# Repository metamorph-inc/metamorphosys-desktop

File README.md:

# metamorphosys-desktop
The **Metamorphosys** tools are used for electronics design and analysis.

_NOTE: This desktop version will soon be replaced by [metamorphosys-web](https://github.com/metamorph-inc/metamorphosys-web). Click over to that repository for a **[live demo](https://github.com/metamorph-inc/metamorphosys-web)**._

# Installer and Documentation
Visit the [alpha release](http://www.metamorphsoftware.com/alpha/) page for:
- Windows Installer
- Example Models
- Walkthrough Tutorials
- Tool Documentation

# Building
To compile the tools from scratch, see [BUILD.md](BUILD.md).

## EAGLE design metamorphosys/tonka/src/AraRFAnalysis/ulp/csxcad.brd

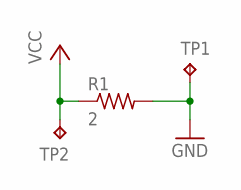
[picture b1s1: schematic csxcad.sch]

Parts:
R1: 2; R0603
TP1, TP2: TPB2,54; B2,54

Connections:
GND: R1.2, TP1.TP
VCC: R1.1, TP2.TP

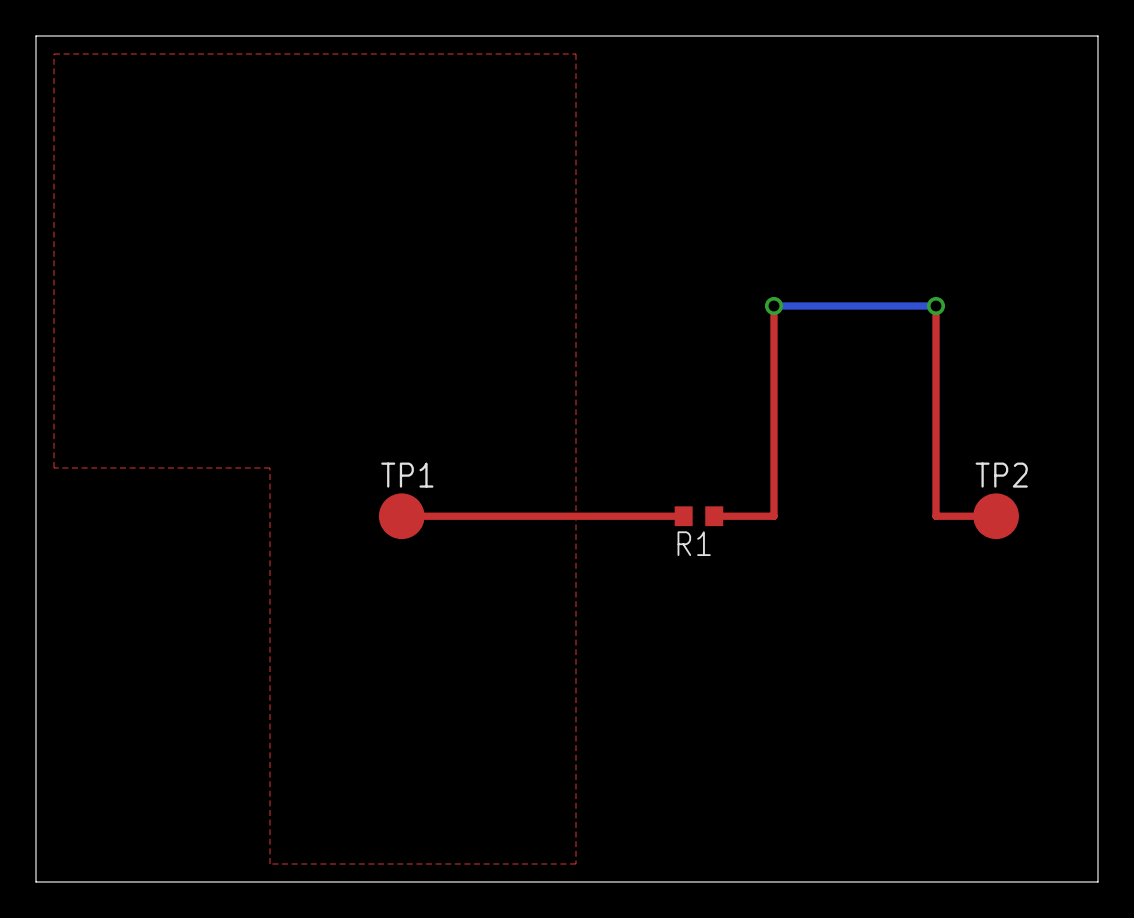
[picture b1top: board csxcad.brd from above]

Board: 2 copper layers, 59.0 x 47.0 mm, 3 parts (0 on the bottom side), 2 nets.

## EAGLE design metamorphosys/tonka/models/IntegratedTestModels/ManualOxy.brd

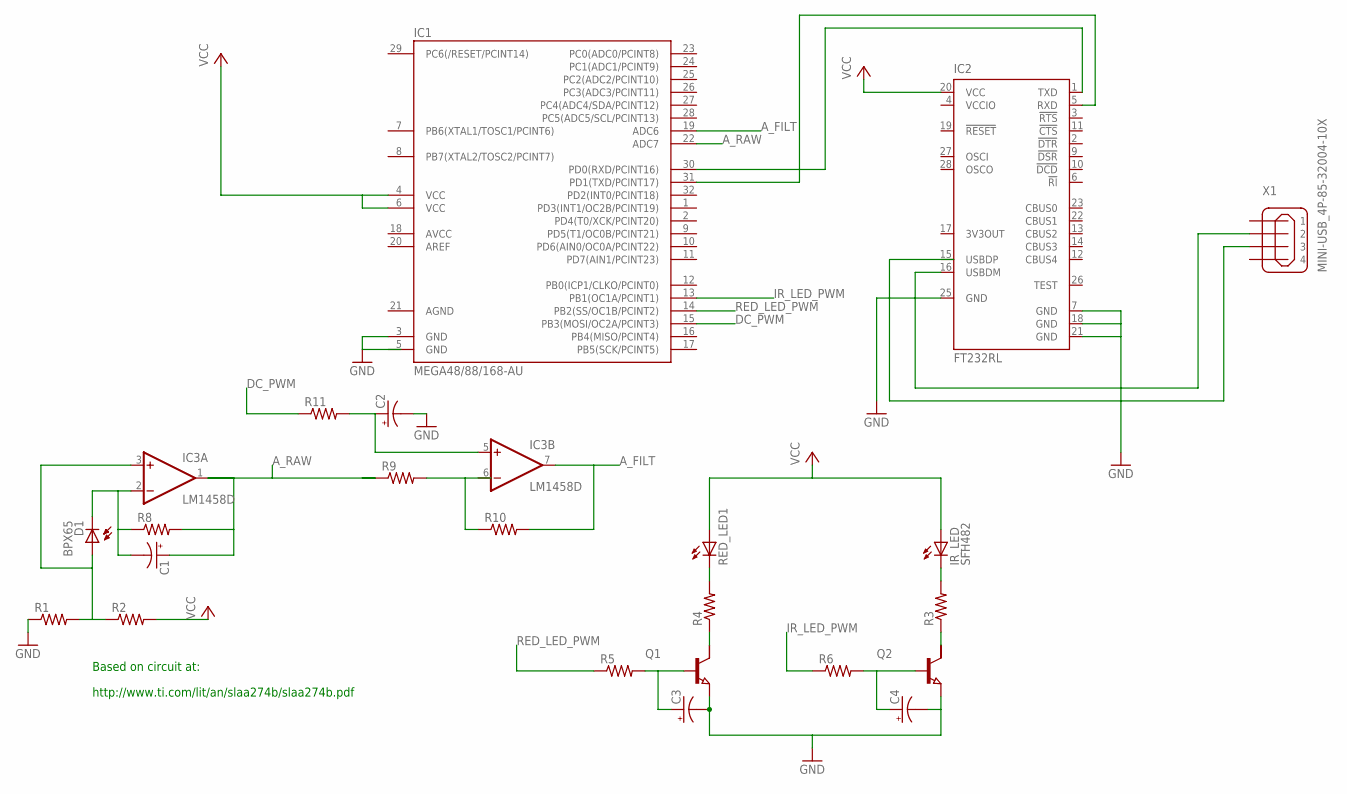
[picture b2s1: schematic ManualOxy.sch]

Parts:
C1, C2, C3, C4: CPOL-US153CLV-0810; 153CLV-0810
D1: BPX65
IC1: MEGA48/88/168-AU; TQFP32-08
IC2: FT232RL; SSOP28
IC3: LM1458D; SO08
IR_LED: SFH482
Q1, Q2: NPN-TRANSISTIOR-2COLSOT143; SOT143
R1, R2, R3, R4, R5, R6, R8, R9, R10, R11: R-US_M2012; M2012
RED_LED1: LED10MM
X1: MINI-USB_4P-85-32004-10X; 85-32004-10X

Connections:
AGND: IC1.21 (AGND)
A_FILT: IC3.7 (OUT), R10.2
A_RAW: C1.+, IC3.1 (OUT), R8.2, R9.1
DC_PWM: IC1.15 (PB3(MOSI/OC2A/PCINT3))
GND: C2.-, C3.-, C4.-, IC1.3 (GND), IC1.5 (GND), IC2.7 (GND), IC2.18 (GND), IC2.21 (GND), IC2.25 (GND), Q1.3 (E), Q2.3 (E), R1.1
IR_LED_PWM: IC1.13 (PB1(OC1A/PCINT1))
unnamed: IC1.30 (PD0(RXD/PCINT16)), IC2.1 (TXD)
unnamed: IC1.31 (PD1(TXD/PCINT17)), IC2.5 (RXD)
unnamed: IC2.16 (USBDM), X1.2
unnamed: Q1.2 (C), R4.1
unnamed: R4.2, RED_LED1.K (C)
unnamed: IR_LED.K (C), R3.2
unnamed: Q2.2 (C), R3.1
unnamed: D1.A, IC3.3 (+IN), R1.2, R2.1
unnamed: C1.-, D1.K (C), IC3.2 (-IN), R8.1
unnamed: R9.2, R10.1
unnamed: C2.+, IC3.5 (+IN), R11.2
unnamed: C3.+, Q1.1 (B), R5.2
unnamed: C4.+, Q2.1 (B), R6.2
RED_LED_PWM: IC1.14 (PB2(SS/OC1B/PCINT2))
V+: IC3.8 (V+)
V-: IC3.4 (V-)
VCC: IC1.4 (VCC), IC1.6 (VCC), IC2.20 (VCC), IR_LED.A, R2.2, RED_LED1.A
VCCIO: IC2.4 (VCCIO)

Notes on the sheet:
http://www.ti.com/lit/an/slaa274b/slaa274b.pdf
Based on circuit at:

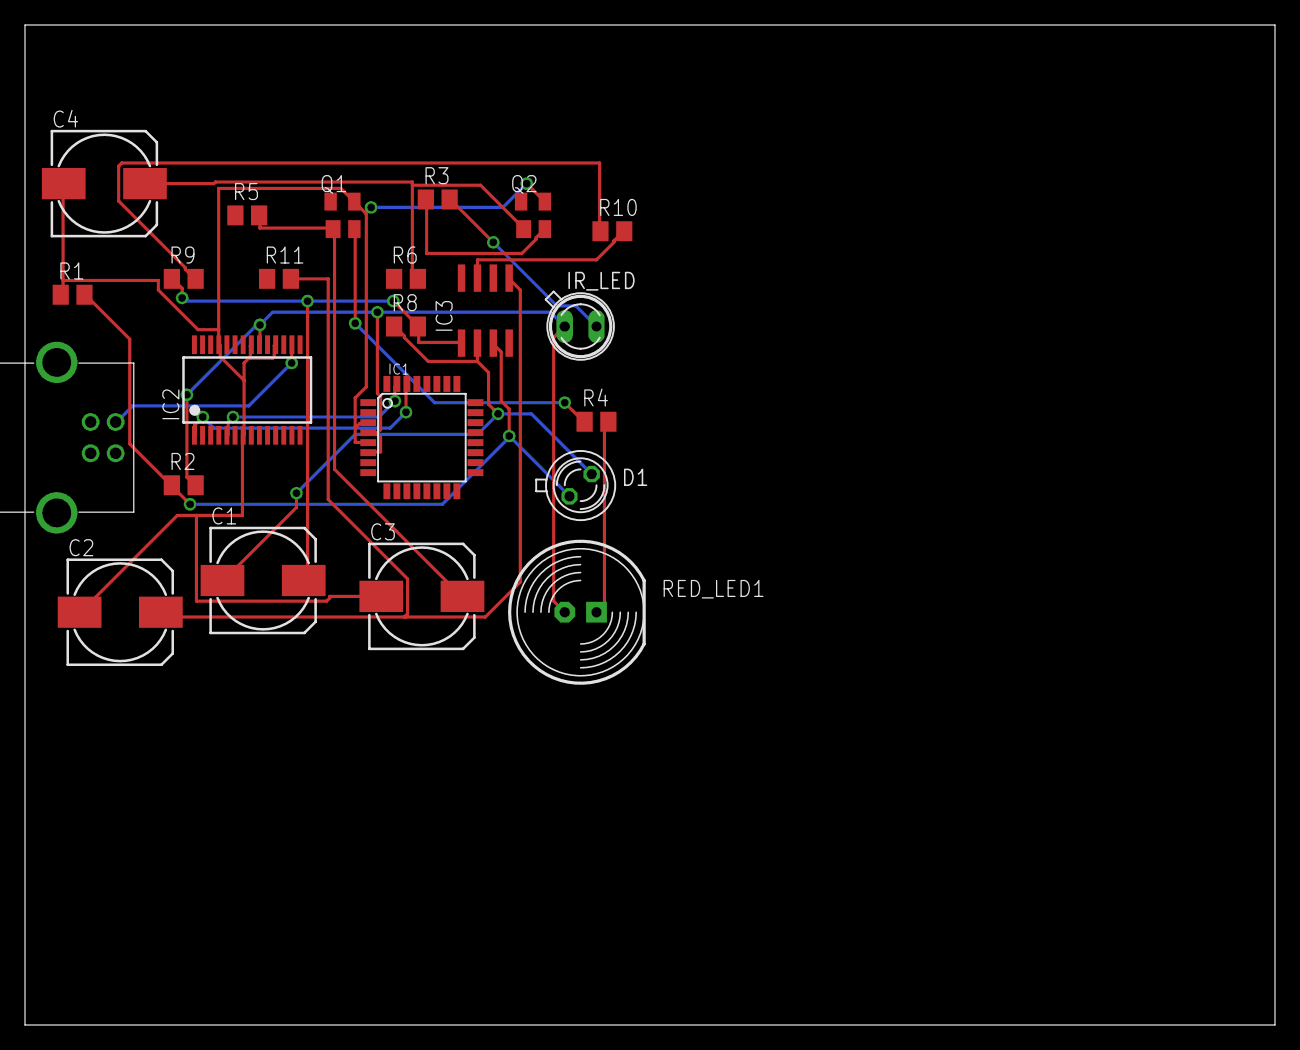
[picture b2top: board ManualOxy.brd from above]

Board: 2 copper layers, 100.0 x 80.0 mm, 23 parts (0 on the bottom side), 17 nets.

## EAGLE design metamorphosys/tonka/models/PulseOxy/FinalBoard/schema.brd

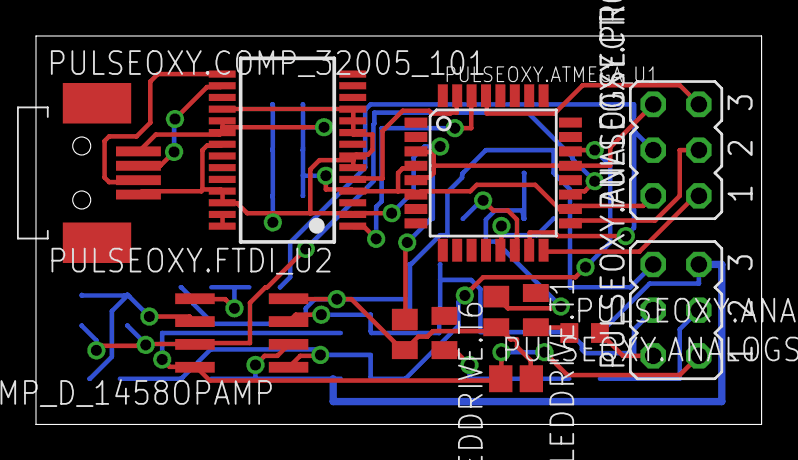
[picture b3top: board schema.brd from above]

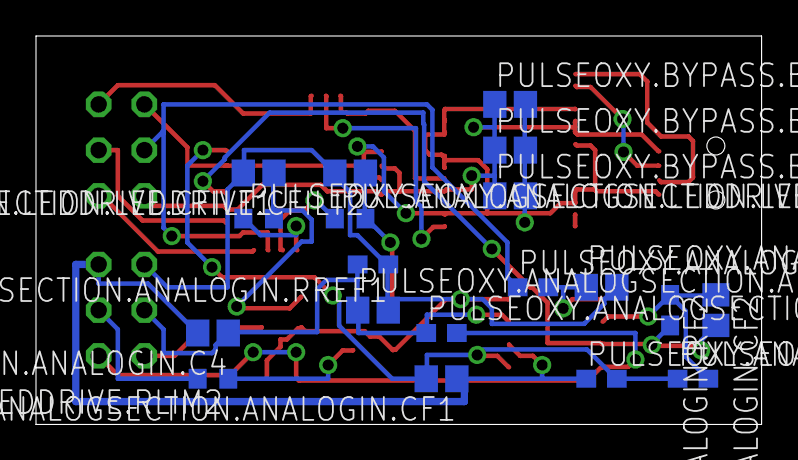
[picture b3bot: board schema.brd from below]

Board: 2 copper layers, 40.3 x 21.6 mm, 29 parts (19 on the bottom side), 27 nets.

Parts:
PULSEOXY.ANALOGSECTION.ANALOGIN.C2, PULSEOXY.ANALOGSECTION.ANALOGIN.C4, PULSEOXY.ANALOGSECTION.ANALOGIN.CBP1, PULSEOXY.ANALOGSECTION.ANALOGIN.CF1, PULSEOXY.ANALOGSECTION.ANALOGIN.CF2, PULSEOXY.ANALOGSECTION.ANALOGIN.CREF, PULSEOXY.ANALOGSECTION.LEDDRIVE.CFILT1, PULSEOXY.ANALOGSECTION.LEDDRIVE.CFILT2, PULSEOXY.BYPASS.BP1, PULSEOXY.BYPASS.BP2, PULSEOXY.BYPASS.BP3: C0805
PULSEOXY.ANALOGSECTION.ANALOGIN.COMP_D_1458OPAMP: LM1458D; SO08
PULSEOXY.ANALOGSECTION.ANALOGIN.R11, PULSEOXY.ANALOGSECTION.ANALOGIN.RF1, PULSEOXY.ANALOGSECTION.ANALOGIN.RF2, PULSEOXY.ANALOGSECTION.ANALOGIN.RI2, PULSEOXY.ANALOGSECTION.ANALOGIN.RREF1, PULSEOXY.ANALOGSECTION.ANALOGIN.RREF2: C0603
PULSEOXY.ANALOGSECTION.LEDDRIVE.RDRIVE1, PULSEOXY.ANALOGSECTION.LEDDRIVE.RDRIVE2, PULSEOXY.ANALOGSECTION.LEDDRIVE.RLIM1, PULSEOXY.ANALOGSECTION.LEDDRIVE.RLIM2: R0603
PULSEOXY.ANALOGSECTION.LEDDRIVE.T1, PULSEOXY.ANALOGSECTION.LEDDRIVE.T6: SOT143
PULSEOXY.ANALOGSECTION.SENSORHEADER, PULSEOXY.PROGRPORT: JP3Q
PULSEOXY.ATMEGA_U1: MEGA48/88/168-AU; TQFP32-08
PULSEOXY.COMP_32005_101: MINI-USB_4P-32005-101; 32005-101
PULSEOXY.FTDI_U2: FT232RL; SSOP28

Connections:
unnamed: PULSEOXY.ANALOGSECTION.ANALOGIN.C2.2, PULSEOXY.ANALOGSECTION.ANALOGIN.CBP1.2, PULSEOXY.ANALOGSECTION.ANALOGIN.COMP_D_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.4, PULSEOXY.ANALOGSECTION.ANALOGIN.CREF.2, PULSEOXY.ANALOGSECTION.ANALOGIN.RREF1.1, PULSEOXY.ANALOGSECTION.LEDDRIVE.CFILT1.2, PULSEOXY.ANALOGSECTION.LEDDRIVE.CFILT2.2, PULSEOXY.ANALOGSECTION.LEDDRIVE.T1.2, PULSEOXY.ANALOGSECTION.LEDDRIVE.T6.2, PULSEOXY.ANALOGSECTION.SENSORHEADER.6
unnamed: PULSEOXY.ANALOGSECTION.ANALOGIN.C2.1, PULSEOXY.ANALOGSECTION.ANALOGIN.COMP_D_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.5, PULSEOXY.ANALOGSECTION.ANALOGIN.R11.2
unnamed: PULSEOXY.ANALOGSECTION.ANALOGIN.C4.2, PULSEOXY.ANALOGSECTION.ANALOGIN.CF1.1, PULSEOXY.ANALOGSECTION.ANALOGIN.COMP_D_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.2, PULSEOXY.ANALOGSECTION.ANALOGIN.RF1.1, PULSEOXY.ANALOGSECTION.SENSORHEADER.5
unnamed: PULSEOXY.ANALOGSECTION.ANALOGIN.C4.1, PULSEOXY.ANALOGSECTION.ANALOGIN.COMP_D_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.3, PULSEOXY.ANALOGSECTION.ANALOGIN.CREF.1, PULSEOXY.ANALOGSECTION.ANALOGIN.RREF1.2, PULSEOXY.ANALOGSECTION.ANALOGIN.RREF2.1, PULSEOXY.ANALOGSECTION.SENSORHEADER.4
unnamed: PULSEOXY.ANALOGSECTION.ANALOGIN.CBP1.1, PULSEOXY.ANALOGSECTION.ANALOGIN.COMP_D_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.8, PULSEOXY.ANALOGSECTION.ANALOGIN.RREF2.2, PULSEOXY.ANALOGSECTION.SENSORHEADER.1
unnamed: PULSEOXY.ANALOGSECTION.ANALOGIN.CF1.2, PULSEOXY.ANALOGSECTION.ANALOGIN.COMP_D_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.1, PULSEOXY.ANALOGSECTION.ANALOGIN.RF1.2, PULSEOXY.ANALOGSECTION.ANALOGIN.RI2.1, PULSEOXY.ATMEGA_U1.22
unnamed: PULSEOXY.ANALOGSECTION.ANALOGIN.CF2.2, PULSEOXY.ANALOGSECTION.ANALOGIN.COMP_D_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.7, PULSEOXY.ANALOGSECTION.ANALOGIN.RF2.2, PULSEOXY.ATMEGA_U1.19
unnamed: PULSEOXY.ANALOGSECTION.ANALOGIN.CF2.1, PULSEOXY.ANALOGSECTION.ANALOGIN.COMP_D_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.6, PULSEOXY.ANALOGSECTION.ANALOGIN.RF2.1, PULSEOXY.ANALOGSECTION.ANALOGIN.RI2.2
unnamed: PULSEOXY.ANALOGSECTION.ANALOGIN.R11.1, PULSEOXY.ATMEGA_U1.15, PULSEOXY.PROGRPORT.4
unnamed: PULSEOXY.ANALOGSECTION.LEDDRIVE.CFILT1.1, PULSEOXY.ANALOGSECTION.LEDDRIVE.RDRIVE1.2, PULSEOXY.ANALOGSECTION.LEDDRIVE.T1.1
unnamed: PULSEOXY.ANALOGSECTION.LEDDRIVE.CFILT2.1, PULSEOXY.ANALOGSECTION.LEDDRIVE.RDRIVE2.2, PULSEOXY.ANALOGSECTION.LEDDRIVE.T6.1
unnamed: PULSEOXY.ANALOGSECTION.LEDDRIVE.RDRIVE1.1, PULSEOXY.ATMEGA_U1.13
unnamed: PULSEOXY.ANALOGSECTION.LEDDRIVE.RDRIVE2.1, PULSEOXY.ATMEGA_U1.14
unnamed: PULSEOXY.ANALOGSECTION.LEDDRIVE.RLIM1.2, PULSEOXY.ANALOGSECTION.SENSORHEADER.2
unnamed: PULSEOXY.ANALOGSECTION.LEDDRIVE.RLIM1.1, PULSEOXY.ANALOGSECTION.LEDDRIVE.T1.3
unnamed: PULSEOXY.ANALOGSECTION.LEDDRIVE.RLIM2.1, PULSEOXY.ANALOGSECTION.LEDDRIVE.T6.3
unnamed: PULSEOXY.ANALOGSECTION.LEDDRIVE.RLIM2.2, PULSEOXY.ANALOGSECTION.SENSORHEADER.3
unnamed: PULSEOXY.ATMEGA_U1.4, PULSEOXY.ATMEGA_U1.6, PULSEOXY.ATMEGA_U1.18, PULSEOXY.BYPASS.BP1.1, PULSEOXY.BYPASS.BP2.1, PULSEOXY.BYPASS.BP3.1, PULSEOXY.COMP_32005_101.1, PULSEOXY.FTDI_U2.4, PULSEOXY.FTDI_U2.19, PULSEOXY.FTDI_U2.20, PULSEOXY.PROGRPORT.2
unnamed: PULSEOXY.ATMEGA_U1.3, PULSEOXY.ATMEGA_U1.5, PULSEOXY.ATMEGA_U1.21, PULSEOXY.BYPASS.BP1.2, PULSEOXY.BYPASS.BP2.2, PULSEOXY.BYPASS.BP3.2, PULSEOXY.COMP_32005_101.4, PULSEOXY.FTDI_U2.2, PULSEOXY.FTDI_U2.6, PULSEOXY.FTDI_U2.7, PULSEOXY.FTDI_U2.9, PULSEOXY.FTDI_U2.10, PULSEOXY.FTDI_U2.11, PULSEOXY.FTDI_U2.18, PULSEOXY.FTDI_U2.21, PULSEOXY.FTDI_U2.25, PULSEOXY.FTDI_U2.26, PULSEOXY.PROGRPORT.6
unnamed: PULSEOXY.ATMEGA_U1.30, PULSEOXY.FTDI_U2.1
unnamed: PULSEOXY.ATMEGA_U1.31, PULSEOXY.FTDI_U2.5
unnamed: PULSEOXY.ATMEGA_U1.29, PULSEOXY.PROGRPORT.5
unnamed: PULSEOXY.ATMEGA_U1.16, PULSEOXY.PROGRPORT.1
unnamed: PULSEOXY.ATMEGA_U1.17, PULSEOXY.PROGRPORT.3
unnamed: PULSEOXY.COMP_32005_101.3, PULSEOXY.FTDI_U2.15
unnamed: PULSEOXY.COMP_32005_101.2, PULSEOXY.FTDI_U2.16
unnamed: PULSEOXY.FTDI_U2.27, PULSEOXY.FTDI_U2.28

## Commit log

2015-01-13 Add build instructions
2015-01-15 snapshot from de626a5<--cc77402
2015-09-11 snapshot from ed42398
2015-09-11 Sync with commit 10825e7
